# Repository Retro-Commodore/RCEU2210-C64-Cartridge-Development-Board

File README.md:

# RCEU2210 - C64 Cartridge Development Board
Another Prototyping cartridge - or developer board

This is used for generic prototyping for which you can make connections soldering wires to the desired pins.

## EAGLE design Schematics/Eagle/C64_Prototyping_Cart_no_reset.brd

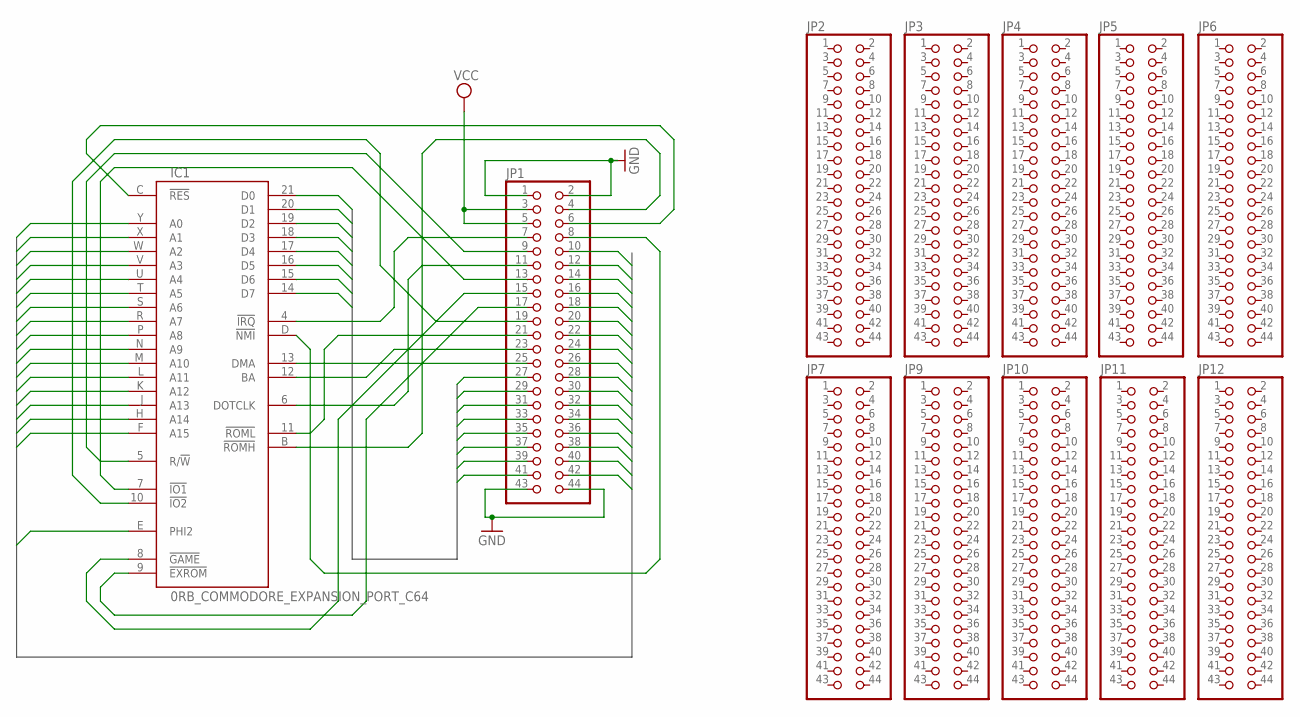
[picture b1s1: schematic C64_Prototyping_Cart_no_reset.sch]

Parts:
IC1: 0RB_COMMODORE_EXPANSION_PORT_C64; 0RB_COMMODORE_MA100-22-2
JP1, JP2, JP3, JP4, JP5, JP6, JP7, JP9, JP10, JP11, JP12: PINHD-2X22; 2X22

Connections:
!EXROM: IC1.9 (!EXROM), JP1.17
!GAME: IC1.8 (!GAME), JP1.15
!IO1: IC1.7 (!IO1), JP1.13
!IO2: IC1.10 (!IO2), JP1.19
!IRQ: IC1.4 (!IRQ), JP1.7
!NMI: IC1.D (!NMI), JP1.8
!RES: IC1.C (!RES), JP1.6
!ROML: IC1.11 (!ROML), JP1.21
A0: IC1.Y (A0), JP1.42
A1: IC1.X (A1), JP1.40
A2: IC1.W (A2), JP1.38
A3: IC1.V (A3), JP1.36
A4: IC1.U (A4), JP1.34
A5: IC1.T (A5), JP1.32
A6: IC1.S (A6), JP1.30
A7: IC1.R (A7), JP1.28
A8: IC1.P (A8), JP1.26
A9: IC1.N (A9), JP1.24
A10: IC1.M (A10), JP1.22
A11: IC1.L (A11), JP1.20
A12: IC1.K (A12), JP1.18
A13: IC1.J (A13), JP1.16
A14: IC1.H (A14), JP1.14
A15: IC1.F (A15), JP1.12
BA: IC1.12 (BA), JP1.23
D0: IC1.21 (D0), JP1.41
D1: IC1.20 (D1), JP1.39
D2: IC1.19 (D2), JP1.37
D3: IC1.18 (D3), JP1.35
D4: IC1.17 (D4), JP1.33
D5: IC1.16 (D5), JP1.31
D6: IC1.15 (D6), JP1.29
D7: IC1.14 (D7), JP1.27
DMA: IC1.13 (DMA), JP1.25
DOTCLK: IC1.6 (DOTCLK), JP1.11
GND: IC1.1 (GND), IC1.22 (GND), IC1.A (GND), IC1.Z (GND), JP1.1, JP1.2, JP1.43, JP1.44
unnamed: IC1.B (!ROMH), JP1.4
PHI2: IC1.E (PHI2), JP1.10
R!W: IC1.5 (R/!W), JP1.9
VCC: IC1.2 (VCC), IC1.3 (VCC), JP1.3, JP1.5

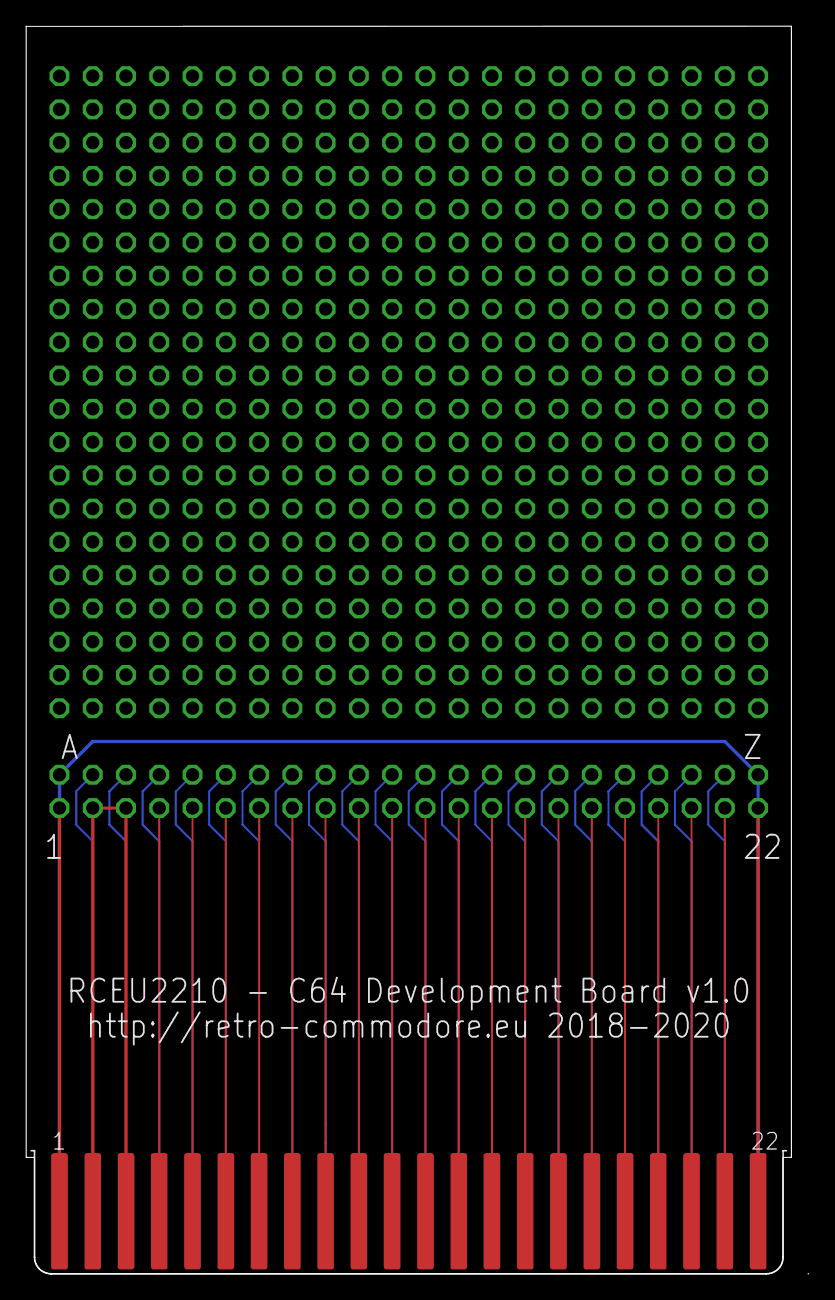
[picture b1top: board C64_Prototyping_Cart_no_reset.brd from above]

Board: 2 copper layers, 59.7 x 95.2 mm, 12 parts (0 on the bottom side), 40 nets.

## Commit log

2020-04-06 Fixing Dirnaming
2020-04-06 Cosmetic changes

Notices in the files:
parts and their libraries:
SparkFun-Aesthetics: Licensing: Creative Commons ShareAlike 4.0 International - https://creativecommons.org/licenses/by-sa/4.0
